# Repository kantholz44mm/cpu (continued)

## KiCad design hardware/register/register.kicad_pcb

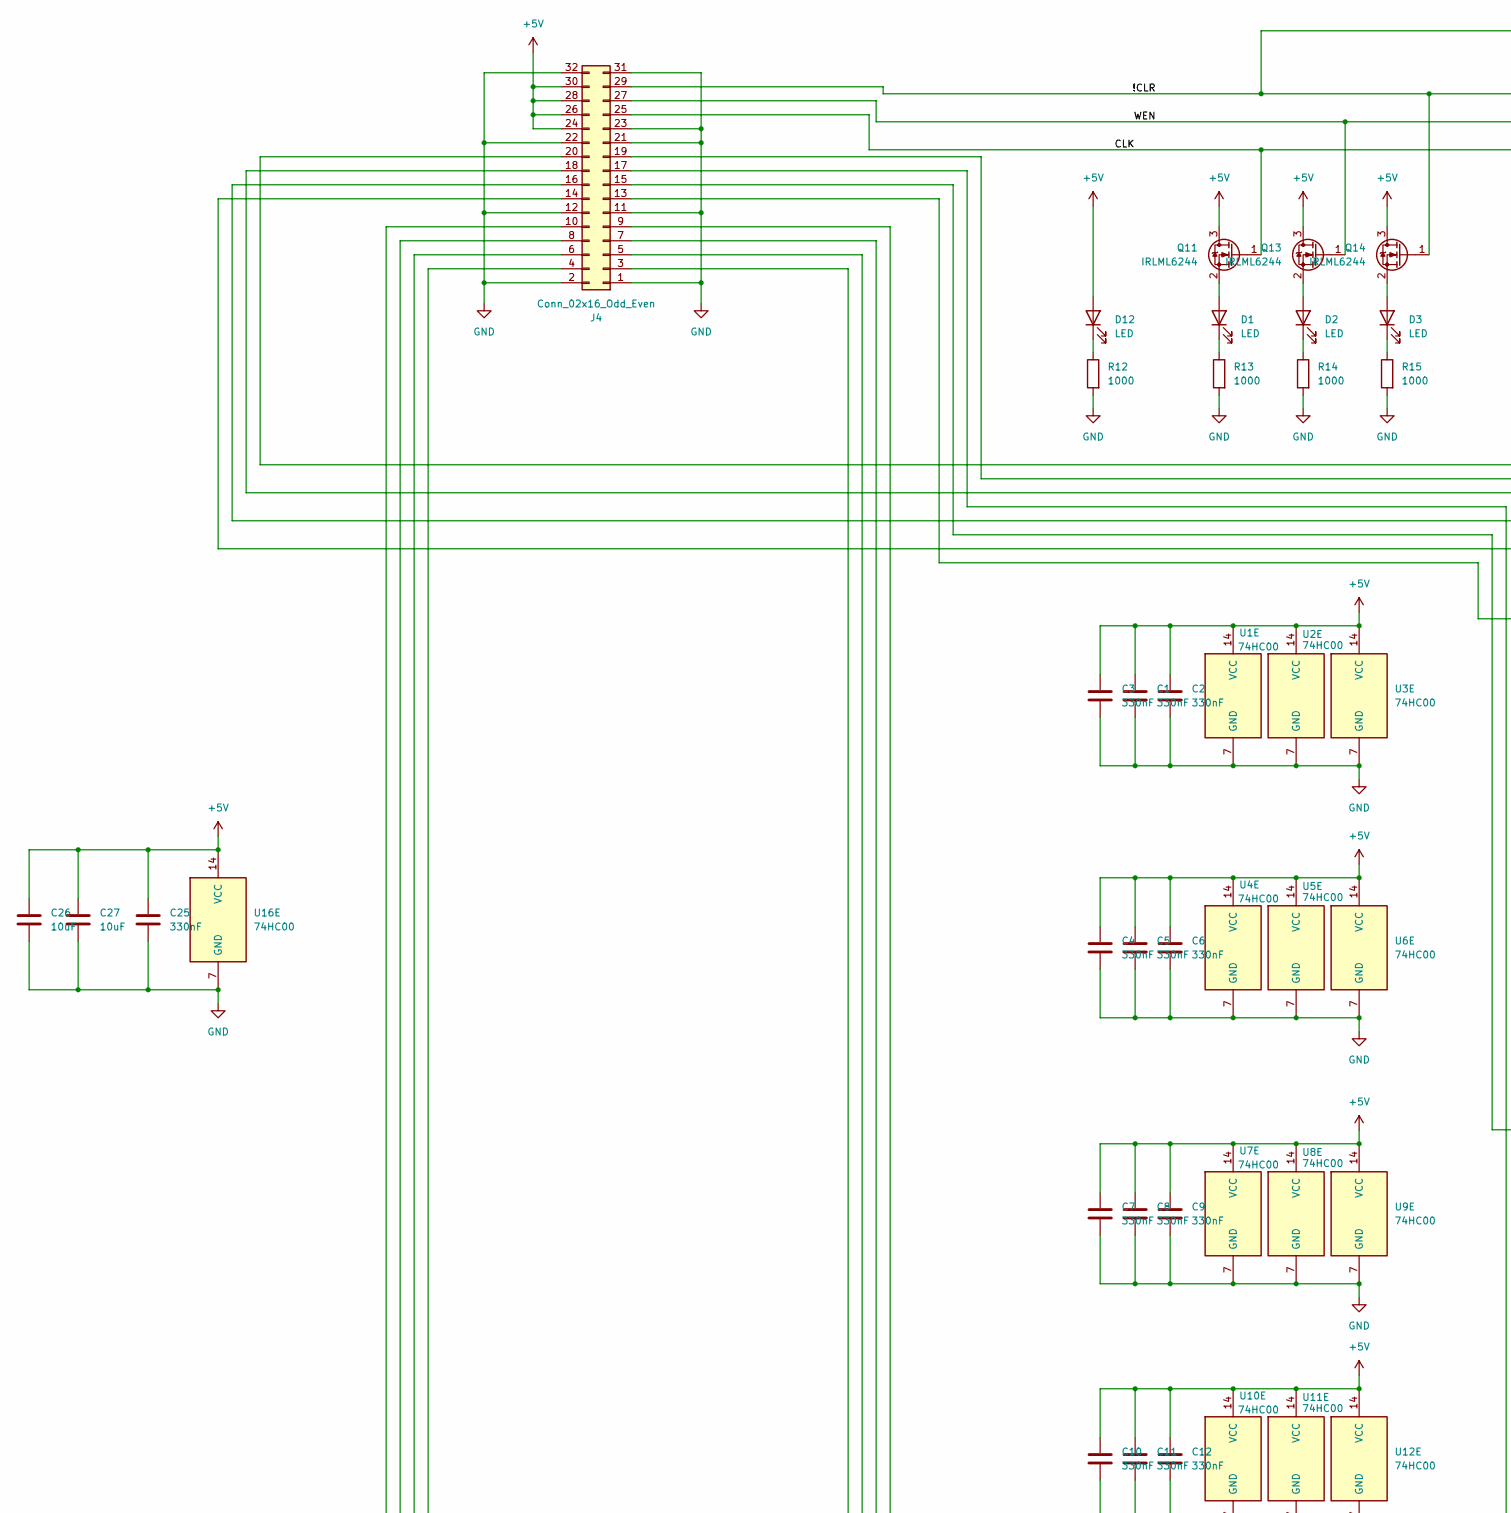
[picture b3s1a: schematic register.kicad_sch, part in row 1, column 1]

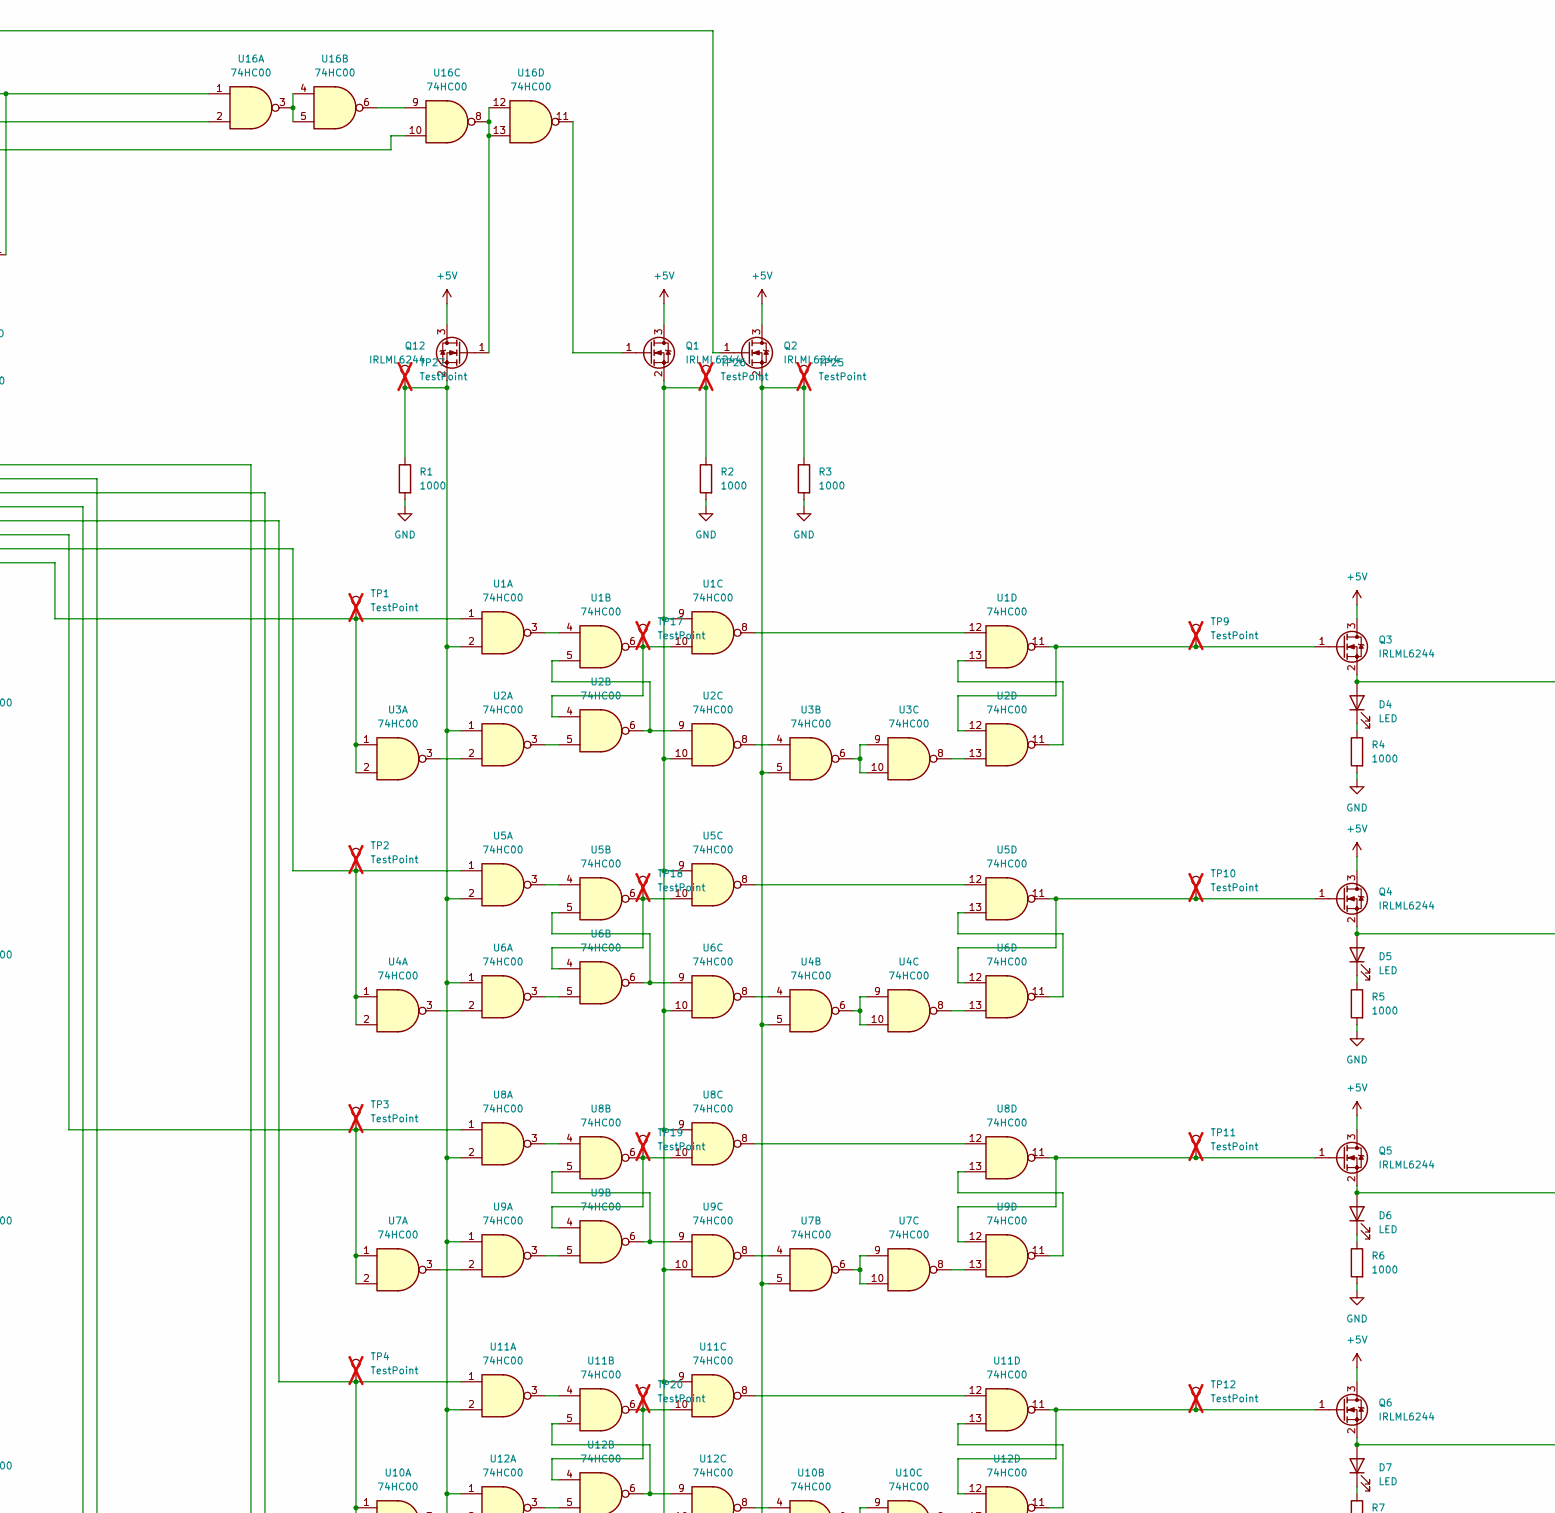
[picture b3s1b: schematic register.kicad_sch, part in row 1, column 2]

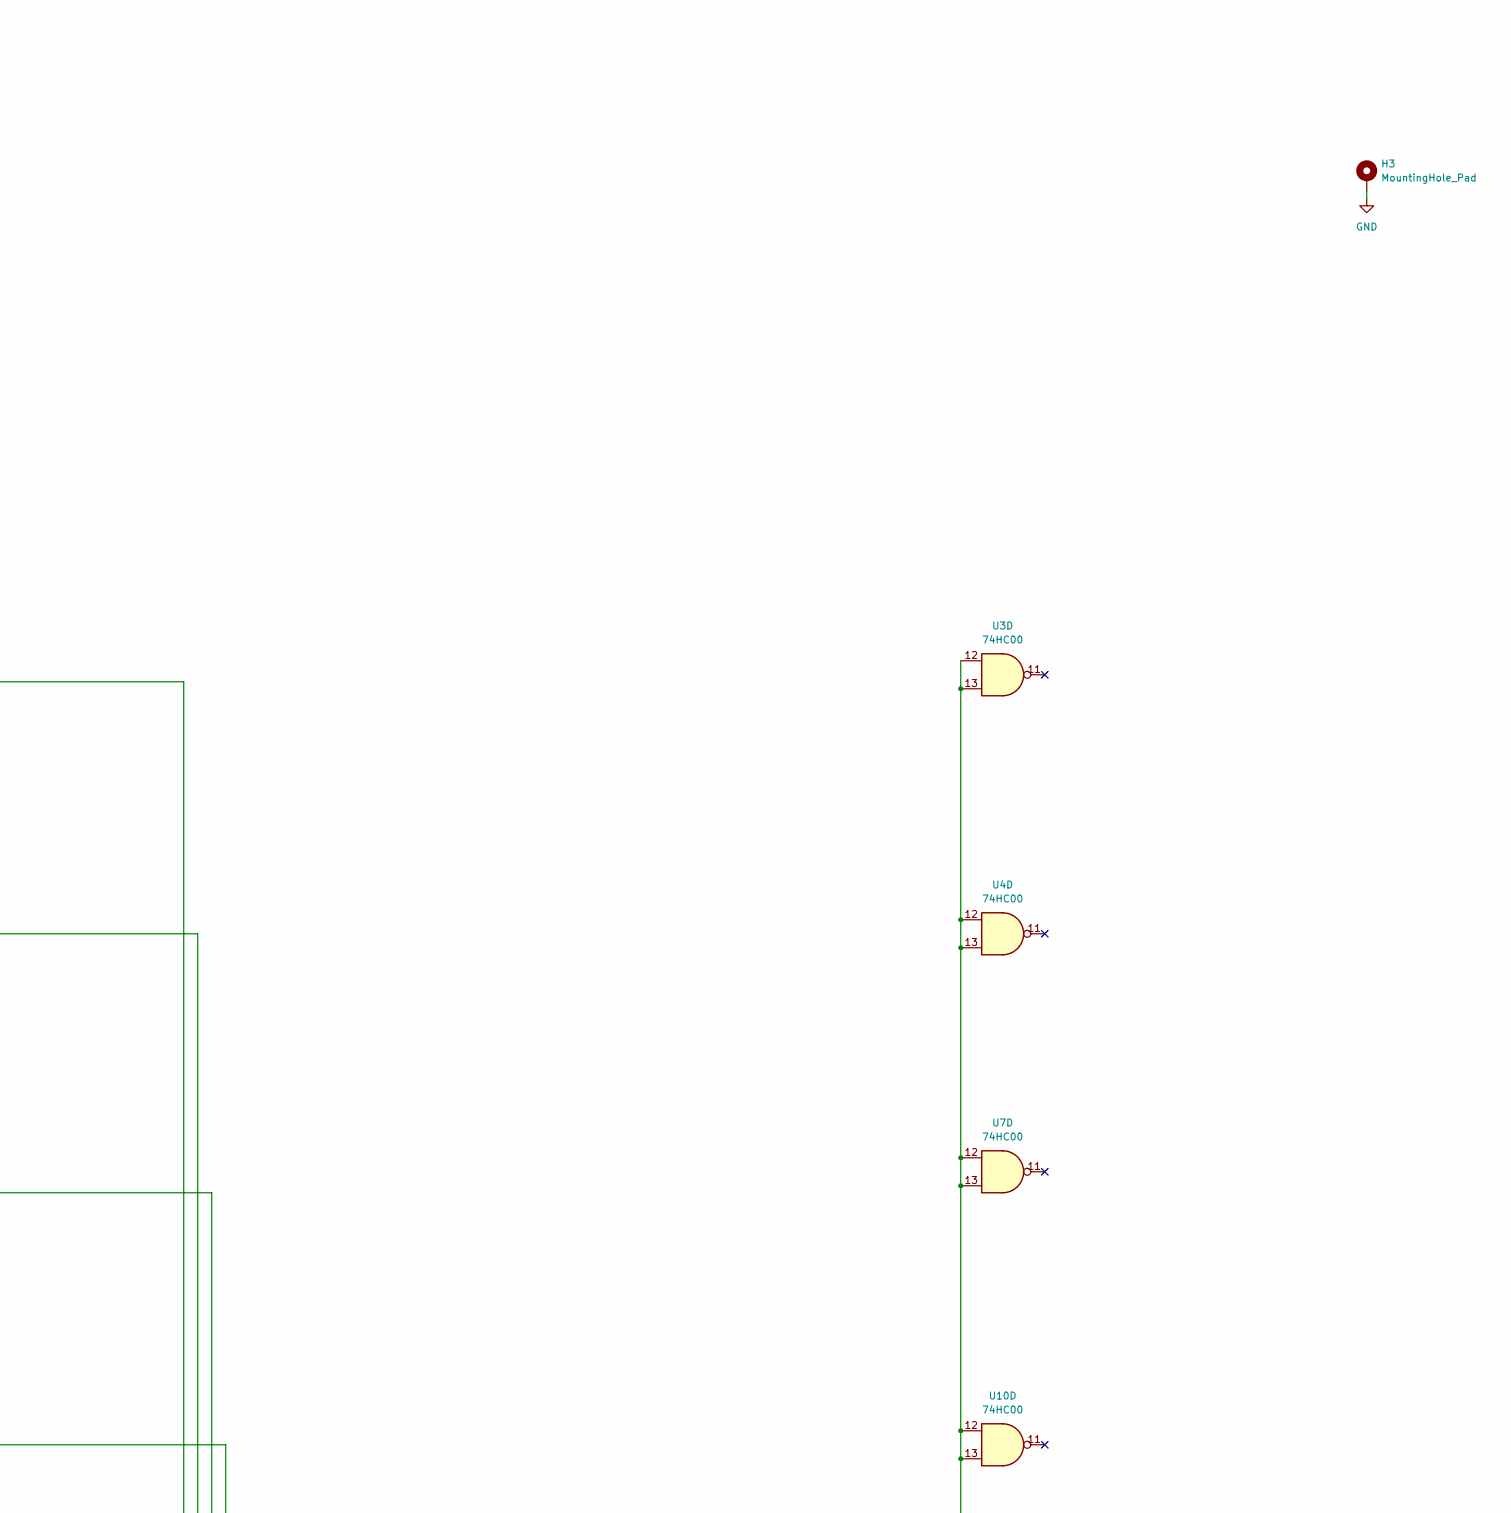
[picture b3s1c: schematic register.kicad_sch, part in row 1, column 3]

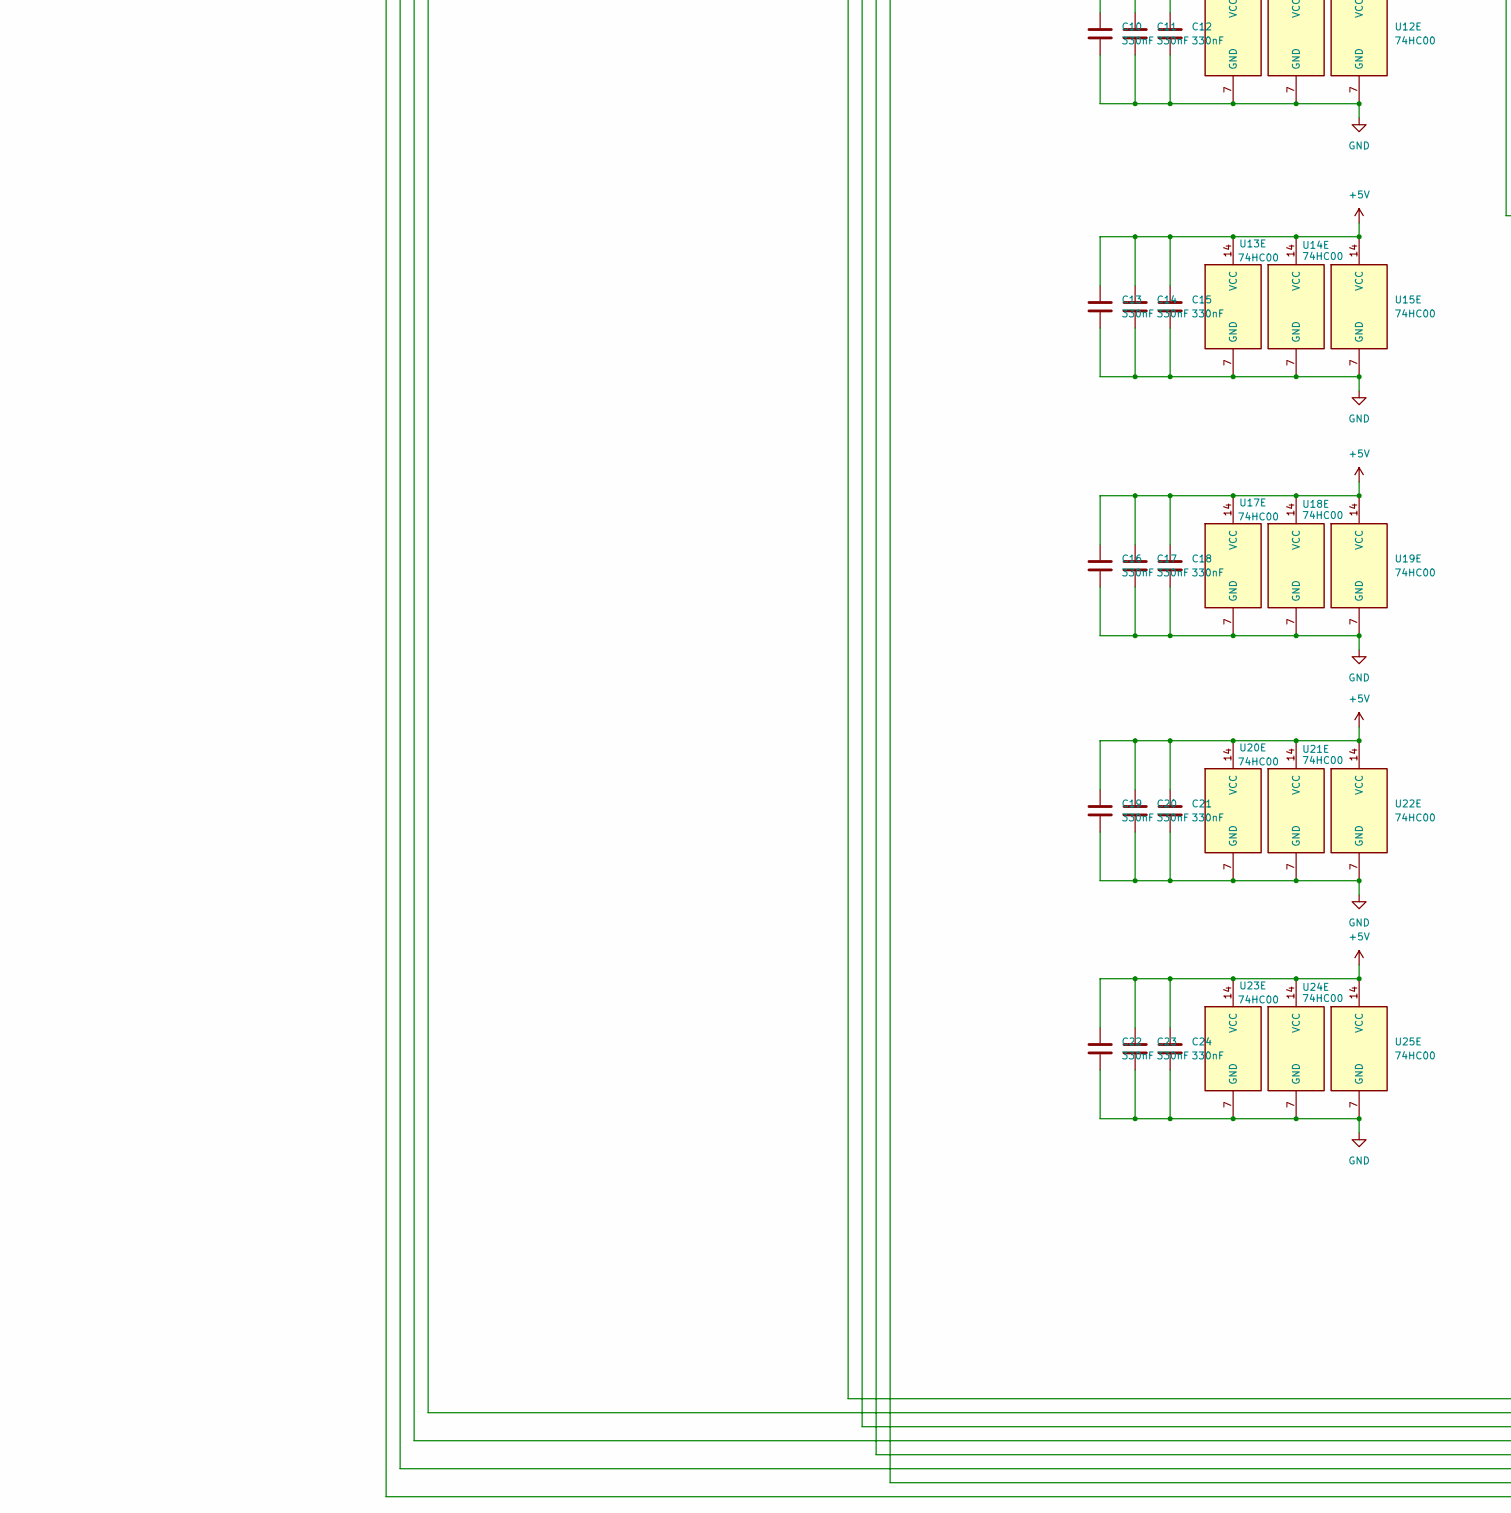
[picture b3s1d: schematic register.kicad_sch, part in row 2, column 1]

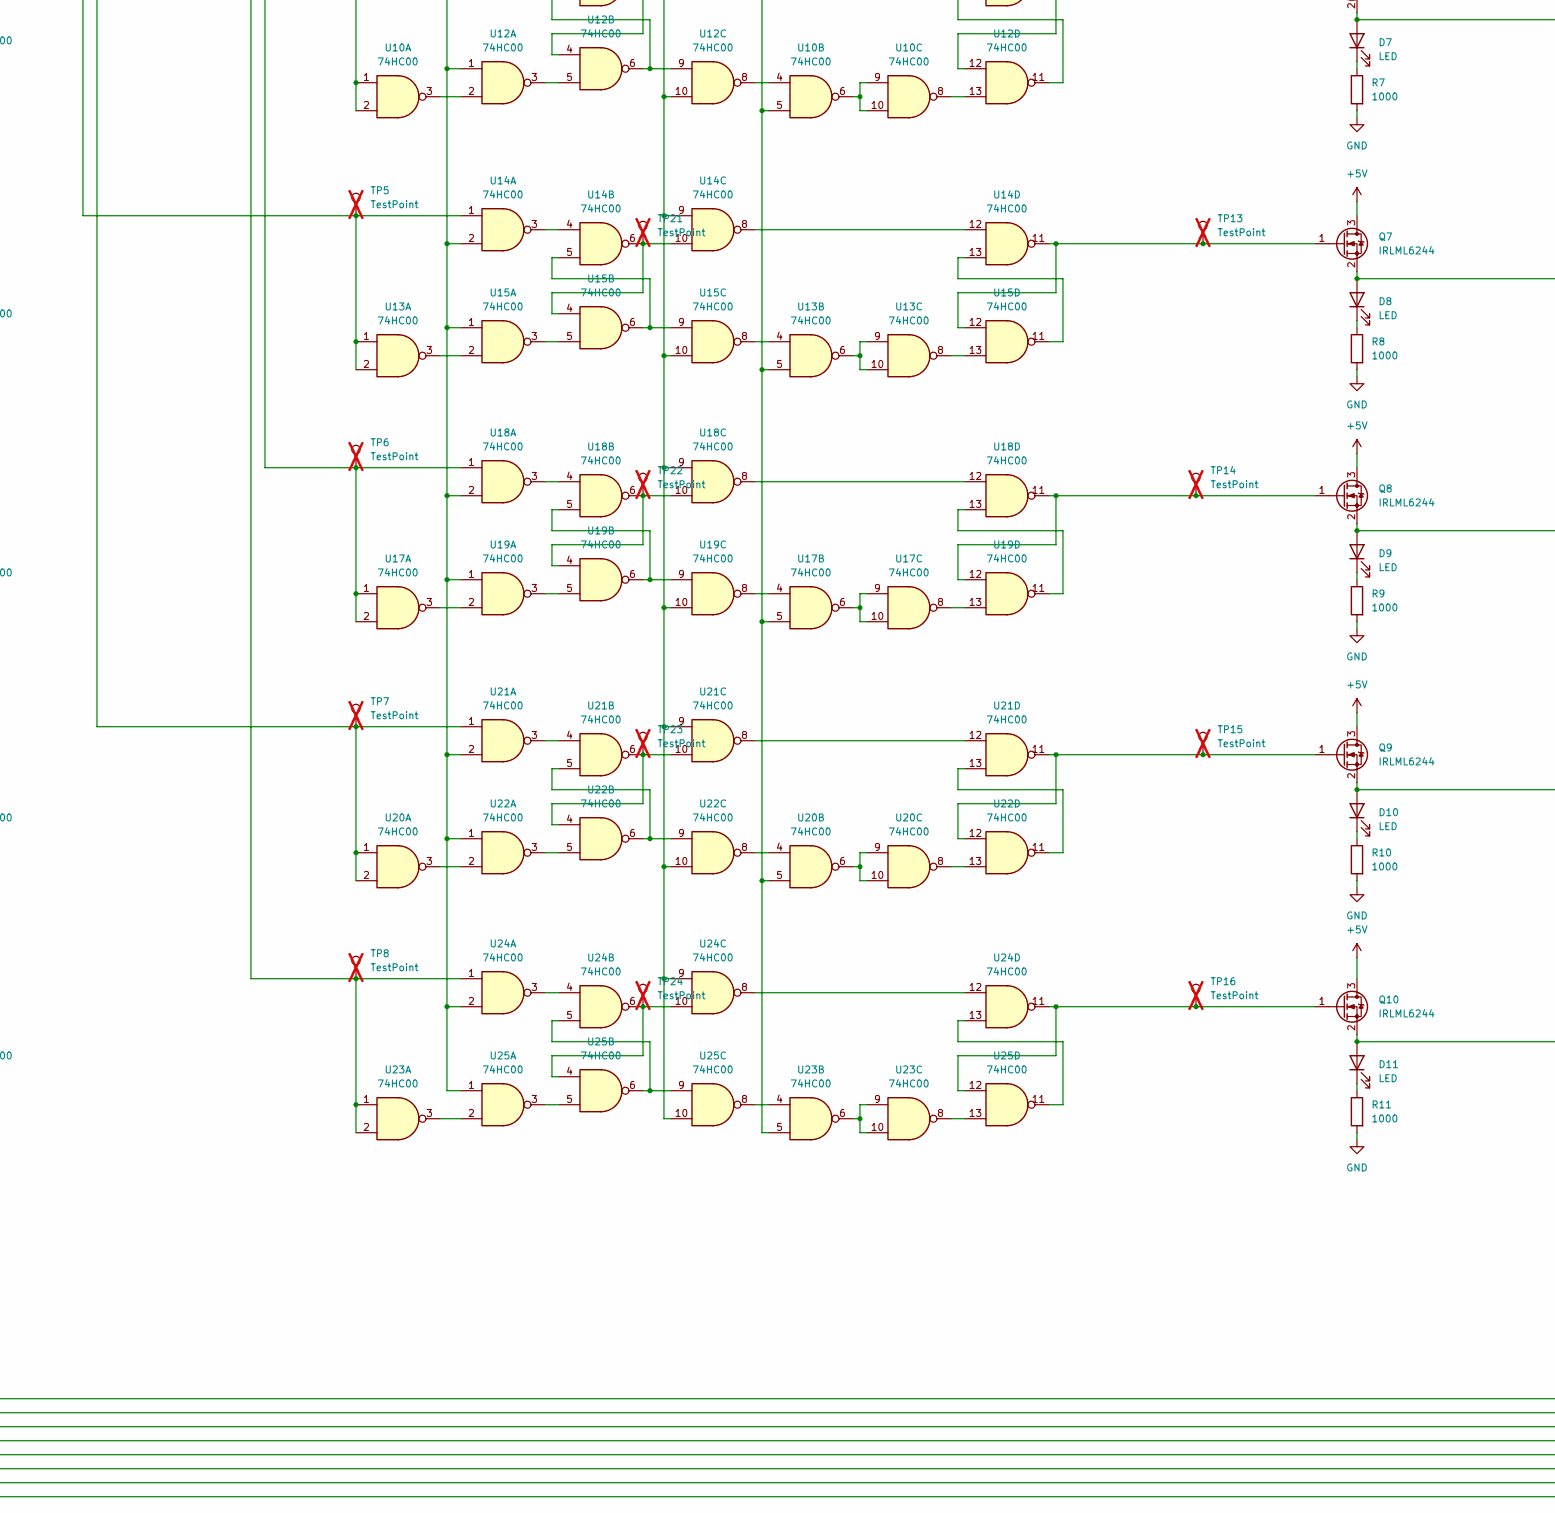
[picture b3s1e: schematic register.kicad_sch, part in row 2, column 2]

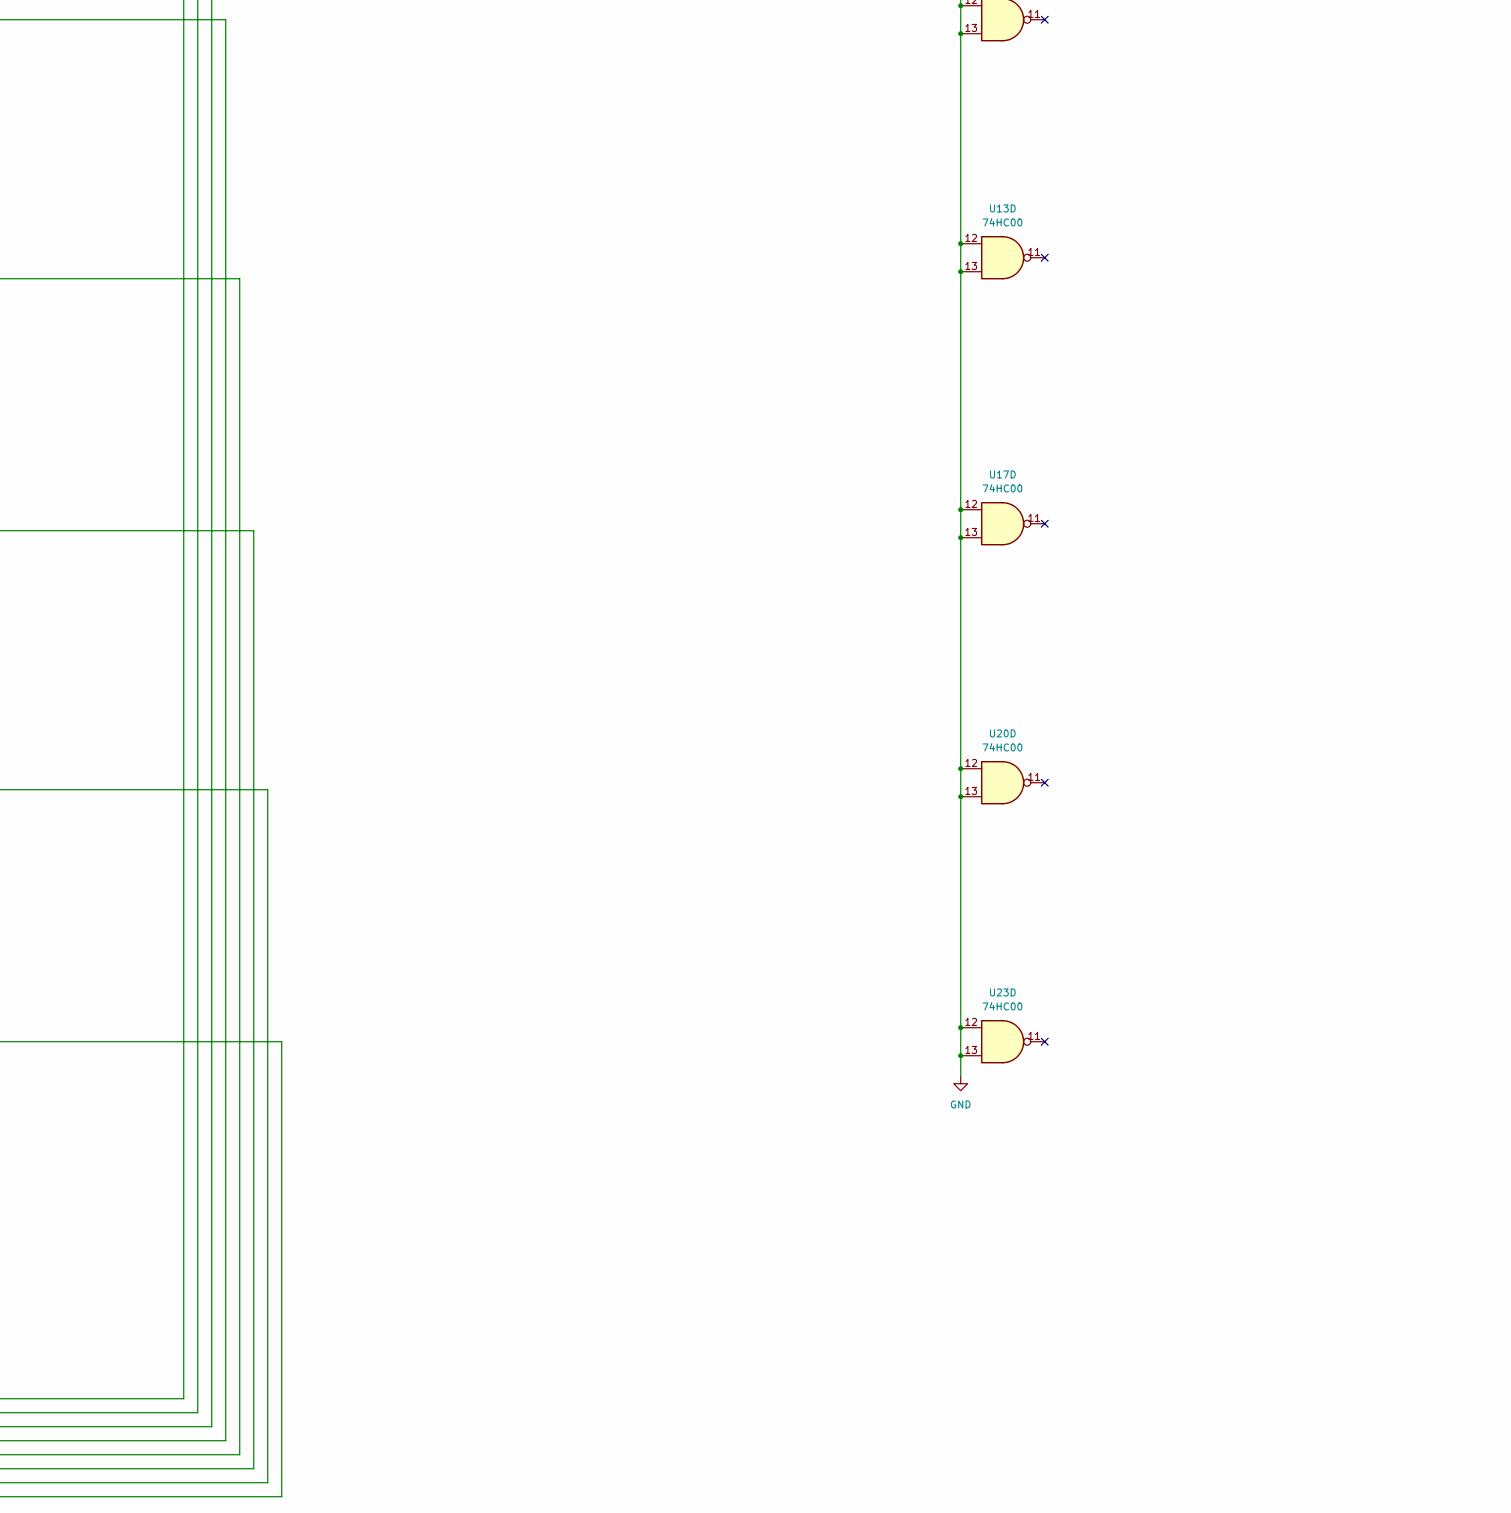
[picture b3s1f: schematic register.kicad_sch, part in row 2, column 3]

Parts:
C1, C2, C3, C4, C5, C6, C7, C8, C9, C10, C11, C12, C13, C14, C15, C16, C17, C18, C19, C20, C21, C22, C23, C24, C25: 330nF; C_0603_1608Metric_Pad1.08x0.95mm_HandSolder; LCSC C2918485
C26, C27: 10uF; C_0603_1608Metric_Pad1.08x0.95mm_HandSolder; LCSC C2909630
D1, D2, D3, D4, D5, D6, D7, D8, D9, D10, D11, D12: LED; LED_0603_1608Metric_Pad1.05x0.95mm_HandSolder; LCSC C84267
H3: MountingHole_Pad; MountingHole_2.2mm_M2_Pad
J4: Conn_02x16_Odd_Even; PinHeader_2x16_P2.54mm_Horizontal
Q1, Q2, Q3, Q4, Q5, Q6, Q7, Q8, Q9, Q10, Q11, Q12, Q13, Q14: IRLML6244; SOT-23_Handsoldering; LCSC C5123965
R1, R2, R3, R4, R5, R6, R7, R8, R9, R10, R11, R12, R13, R14, R15: 1000; R_0603_1608Metric_Pad0.98x0.95mm_HandSolder; LCSC C21190
TP1, TP2, TP3, TP4, TP5, TP6, TP7, TP8, TP9, TP10, TP11, TP12, TP13, TP14, TP15, TP16, TP17, TP18, TP19, TP20, TP21, TP22, TP23, TP24, TP25, TP26, TP27: TestPoint; TestPoint_Pad_D2.0mm; not fitted
U1, U2, U3, U4, U5, U6, U7, U8, U9, U10, U11, U12, U13, U14, U15, U16, U17, U18, U19, U20, U21, U22, U23, U24, U25: 74HC00; SOIC-14_3.9x8.7mm_P1.27mm; LCSC C5586

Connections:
+5V: C1.1, C2.1, C3.1, C4.1, C5.1, C6.1, C7.1, C8.1, C9.1, C10.1, C11.1, C12.1, C13.1, C14.1, C15.1, C16.1, C17.1, C18.1, C19.1, C20.1, C21.1, C22.1, C23.1, C24.1, C25.1, C26.1, C27.1, D12.2 (A), J4.24, J4.26, J4.28, J4.30, Q1.3 (D), Q2.3 (D), Q3.3 (D), Q4.3 (D), Q5.3 (D), Q6.3 (D), Q7.3 (D), Q8.3 (D), Q9.3 (D), Q10.3 (D), Q11.3 (D), Q12.3 (D), Q13.3 (D), Q14.3 (D), U1.14 (VCC), U2.14 (VCC), U3.14 (VCC), U4.14 (VCC), U5.14 (VCC), U6.14 (VCC), U7.14 (VCC), U8.14 (VCC), U9.14 (VCC), U10.14 (VCC), U11.14 (VCC), U12.14 (VCC), U13.14 (VCC), U14.14 (VCC), U15.14 (VCC), U16.14 (VCC), U17.14 (VCC), U18.14 (VCC), U19.14 (VCC), U20.14 (VCC), U21.14 (VCC), U22.14 (VCC), U23.14 (VCC), U24.14 (VCC), U25.14 (VCC)
/!CLR: J4.29, Q2.1 (G), Q14.1 (G), U16.1
/CLK: J4.25, Q11.1 (G), U16.10
/WEN: J4.27, Q13.1 (G), U16.2
GND: C1.2, C2.2, C3.2, C4.2, C5.2, C6.2, C7.2, C8.2, C9.2, C10.2, C11.2, C12.2, C13.2, C14.2, C15.2, C16.2, C17.2, C18.2, C19.2, C20.2, C21.2, C22.2, C23.2, C24.2, C25.2, C26.2, C27.2, H3.1, J4.1, J4.2, J4.11, J4.12, J4.21, J4.22, J4.23, J4.31, J4.32, R1.2, R2.2, R3.2, R4.2, R5.2, R6.2, R7.2, R8.2, R9.2, R10.2, R11.2, R12.2, R13.2, R14.2, R15.2, U1.7 (GND), U2.7 (GND), U3.7 (GND), U3.12, U3.13, U4.7 (GND), U4.12, U4.13, U5.7 (GND), U6.7 (GND), U7.7 (GND), U7.12, U7.13, U8.7 (GND), U9.7 (GND), U10.7 (GND), U10.12, U10.13, U11.7 (GND), U12.7 (GND), U13.7 (GND), U13.12, U13.13, U14.7 (GND), U15.7 (GND), U16.7 (GND), U17.7 (GND), U17.12, U17.13, U18.7 (GND), U19.7 (GND), U20.7 (GND), U20.12, U20.13, U21.7 (GND), U22.7 (GND), U23.7 (GND), U23.12, U23.13, U24.7 (GND), U25.7 (GND)
unnamed: D1.2 (A), Q11.2 (S)
unnamed: D1.1 (K), R13.1
unnamed: D2.2 (A), Q13.2 (S)
unnamed: D2.1 (K), R14.1
unnamed: D3.2 (A), Q14.2 (S)
unnamed: D3.1 (K), R15.1
unnamed: D4.2 (A), J4.3, Q3.2 (S)
unnamed: D4.1 (K), R4.1
unnamed: D5.2 (A), J4.4, Q4.2 (S)
unnamed: D5.1 (K), R5.1
unnamed: D6.2 (A), J4.5, Q5.2 (S)
unnamed: D6.1 (K), R6.1
unnamed: D7.2 (A), J4.6, Q6.2 (S)
unnamed: D7.1 (K), R7.1
unnamed: D8.2 (A), J4.7, Q7.2 (S)
unnamed: D8.1 (K), R8.1
unnamed: D9.2 (A), J4.8, Q8.2 (S)
unnamed: D9.1 (K), R9.1
unnamed: D10.2 (A), J4.9, Q9.2 (S)
unnamed: D10.1 (K), R10.1
unnamed: D11.2 (A), J4.10, Q10.2 (S)
unnamed: D11.1 (K), R11.1
unnamed: D12.1 (K), R12.1
unnamed: J4.13, TP1.1, U1.1, U3.1, U3.2
unnamed: J4.14, TP2.1, U4.1, U4.2, U5.1
unnamed: J4.15, TP3.1, U7.1, U7.2, U8.1
unnamed: J4.16, TP4.1, U10.1, U10.2, U11.1
unnamed: J4.17, TP5.1, U13.1, U13.2, U14.1
unnamed: J4.18, TP6.1, U17.1, U17.2, U18.1
unnamed: J4.19, TP7.1, U20.1, U20.2, U21.1
unnamed: J4.20, TP8.1, U23.1, U23.2, U24.1
unnamed: Q1.1 (G), U16.11
unnamed: Q1.2 (S), R2.1, TP26.1, U1.9, U2.10, U5.9, U6.10, U8.9, U9.10, U11.9, U12.10, U14.9, U15.10, U18.9, U19.10, U21.9, U22.10, U24.9, U25.10
unnamed: Q2.2 (S), R3.1, TP25.1, U3.5, U4.5, U7.5, U10.5, U13.5, U17.5, U20.5, U23.5
unnamed: Q3.1 (G), TP9.1, U1.11, U2.12
unnamed: Q4.1 (G), TP10.1, U5.11, U6.12
unnamed: Q5.1 (G), TP11.1, U8.11, U9.12
unnamed: Q6.1 (G), TP12.1, U11.11, U12.12
unnamed: Q7.1 (G), TP13.1, U14.11, U15.12
unnamed: Q8.1 (G), TP14.1, U18.11, U19.12
unnamed: Q9.1 (G), TP15.1, U21.11, U22.12
unnamed: Q10.1 (G), TP16.1, U24.11, U25.12
unnamed: Q12.1 (G), U16.8, U16.12, U16.13
unnamed: Q12.2 (S), R1.1, TP27.1, U1.2, U2.1, U5.2, U6.1, U8.2, U9.1, U11.2, U12.1, U14.2, U15.1, U18.2, U19.1, U21.2, U22.1, U24.2, U25.1
unnamed: TP17.1, U1.6, U1.10, U2.4
unnamed: TP18.1, U5.6, U5.10, U6.4
unnamed: TP19.1, U8.6, U8.10, U9.4
unnamed: TP20.1, U11.6, U11.10, U12.4
unnamed: TP21.1, U14.6, U14.10, U15.4
unnamed: TP22.1, U18.6, U18.10, U19.4
unnamed: TP23.1, U21.6, U21.10, U22.4
unnamed: TP24.1, U24.6, U24.10, U25.4
unnamed: U1.3, U1.4
unnamed: U1.5, U2.6, U2.9
unnamed: U1.8, U1.12
unnamed: U1.13, U2.11
unnamed: U2.2, U3.3
unnamed: U2.3, U2.5
unnamed: U2.8, U3.4
unnamed: U2.13, U3.8
unnamed: U3.6, U3.9, U3.10
unnamed: U4.3, U6.2
unnamed: U4.4, U6.8
unnamed: U4.8, U6.13
unnamed: U4.6, U4.9, U4.10
unnamed: U5.3, U5.4
unnamed: U5.5, U6.6, U6.9
unnamed: U5.8, U5.12
unnamed: U5.13, U6.11
unnamed: U6.3, U6.5
unnamed: U7.3, U9.2
unnamed: U7.4, U9.8
unnamed: U7.8, U9.13
unnamed: U7.6, U7.9, U7.10
unnamed: U8.3, U8.4
unnamed: U8.5, U9.6, U9.9
unnamed: U8.8, U8.12
unnamed: U8.13, U9.11
unnamed: U9.3, U9.5
unnamed: U10.3, U12.2
unnamed: U10.4, U12.8
unnamed: U10.8, U12.13
unnamed: U10.6, U10.9, U10.10
unnamed: U11.3, U11.4
unnamed: U11.5, U12.6, U12.9
unnamed: U11.8, U11.12
unnamed: U11.13, U12.11
unnamed: U12.3, U12.5
unnamed: U13.3, U15.2
unnamed: U13.4, U15.8
unnamed: U13.8, U15.13
unnamed: U13.6, U13.9, U13.10
unnamed: U14.3, U14.4
unnamed: U14.5, U15.6, U15.9
unnamed: U14.8, U14.12
unnamed: U14.13, U15.11
unnamed: U15.3, U15.5
unnamed: U16.3, U16.4, U16.5
unnamed: U16.6, U16.9
unnamed: U17.3, U19.2
unnamed: U17.4, U19.8
unnamed: U17.8, U19.13
unnamed: U17.6, U17.9, U17.10
unnamed: U18.3, U18.4
unnamed: U18.5, U19.6, U19.9
unnamed: U18.8, U18.12
unnamed: U18.13, U19.11
unnamed: U19.3, U19.5
unnamed: U20.3, U22.2
unnamed: U20.4, U22.8
unnamed: U20.8, U22.13
unnamed: U20.6, U20.9, U20.10
unnamed: U21.3, U21.4
unnamed: U21.5, U22.6, U22.9
unnamed: U21.8, U21.12
unnamed: U21.13, U22.11
unnamed: U22.3, U22.5
unnamed: U23.3, U25.2
unnamed: U23.4, U25.8
unnamed: U23.8, U25.13
unnamed: U23.6, U23.9, U23.10
unnamed: U24.3, U24.4
unnamed: U24.5, U25.6, U25.9
unnamed: U24.8, U24.12
unnamed: U24.13, U25.11
unnamed: U25.3, U25.5

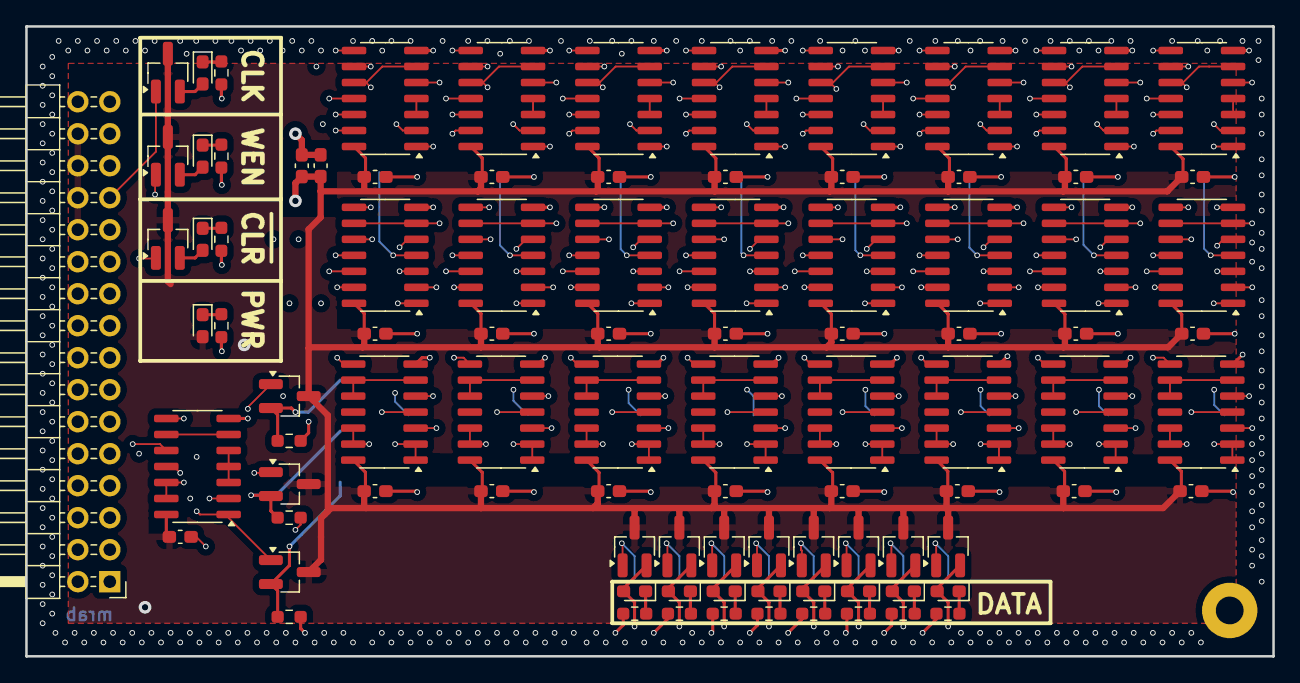
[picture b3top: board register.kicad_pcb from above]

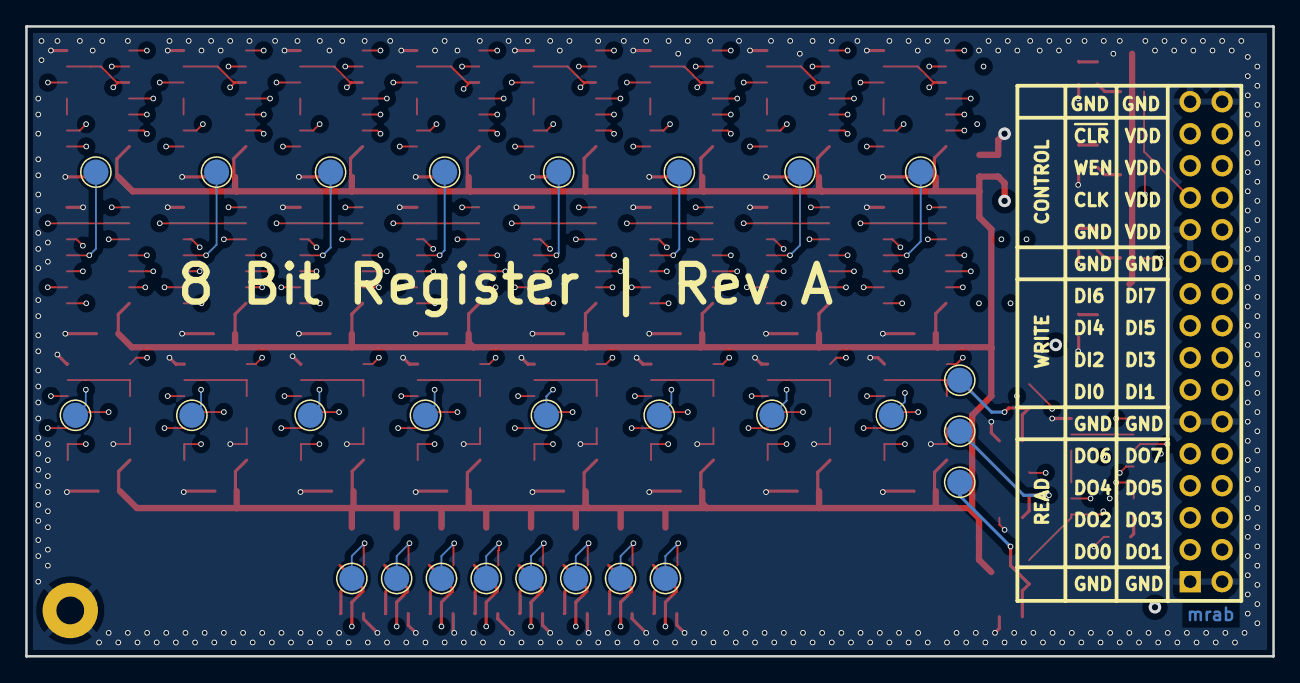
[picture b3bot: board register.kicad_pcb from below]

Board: 4 copper layers, 99.0 x 50.0 mm, 122 parts (27 on the bottom side), 131 nets.

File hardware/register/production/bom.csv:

Designator,Footprint,Quantity,Value,LCSC Part #
"C1, C10, C11, C12, C13, C14, C15, C16, C17, C18, C19, C2, C20, C21, C22, C23, C24, C25, C3, C4, C5, C6, C7, C8, C9",0603,25,330nF,C2918485
"C26, C27",0603,2,10uF,C2909630
"D1, D10, D11, D12, D2, D3, D4, D5, D6, D7, D8, D9",0603,12,LED,C84267
"Q1, Q10, Q11, Q12, Q13, Q14, Q2, Q3, Q4, Q5, Q6, Q7, Q8, Q9",SOT-23_Handsoldering,14,IRLML6244,C5123965
"R1, R10, R11, R12, R13, R14, R15, R2, R3, R4, R5, R6, R7, R8, R9",0603,15,1000,C21190
"U1, U10, U11, U12, U13, U14, U15, U16, U17, U18, U19, U2, U20, U21, U22, U23, U24, U25, U3, U4, U5, U6, U7, U8, U9",SOIC-14_3.9x8.7mm_P1.27mm,25,74HC00,C5586
